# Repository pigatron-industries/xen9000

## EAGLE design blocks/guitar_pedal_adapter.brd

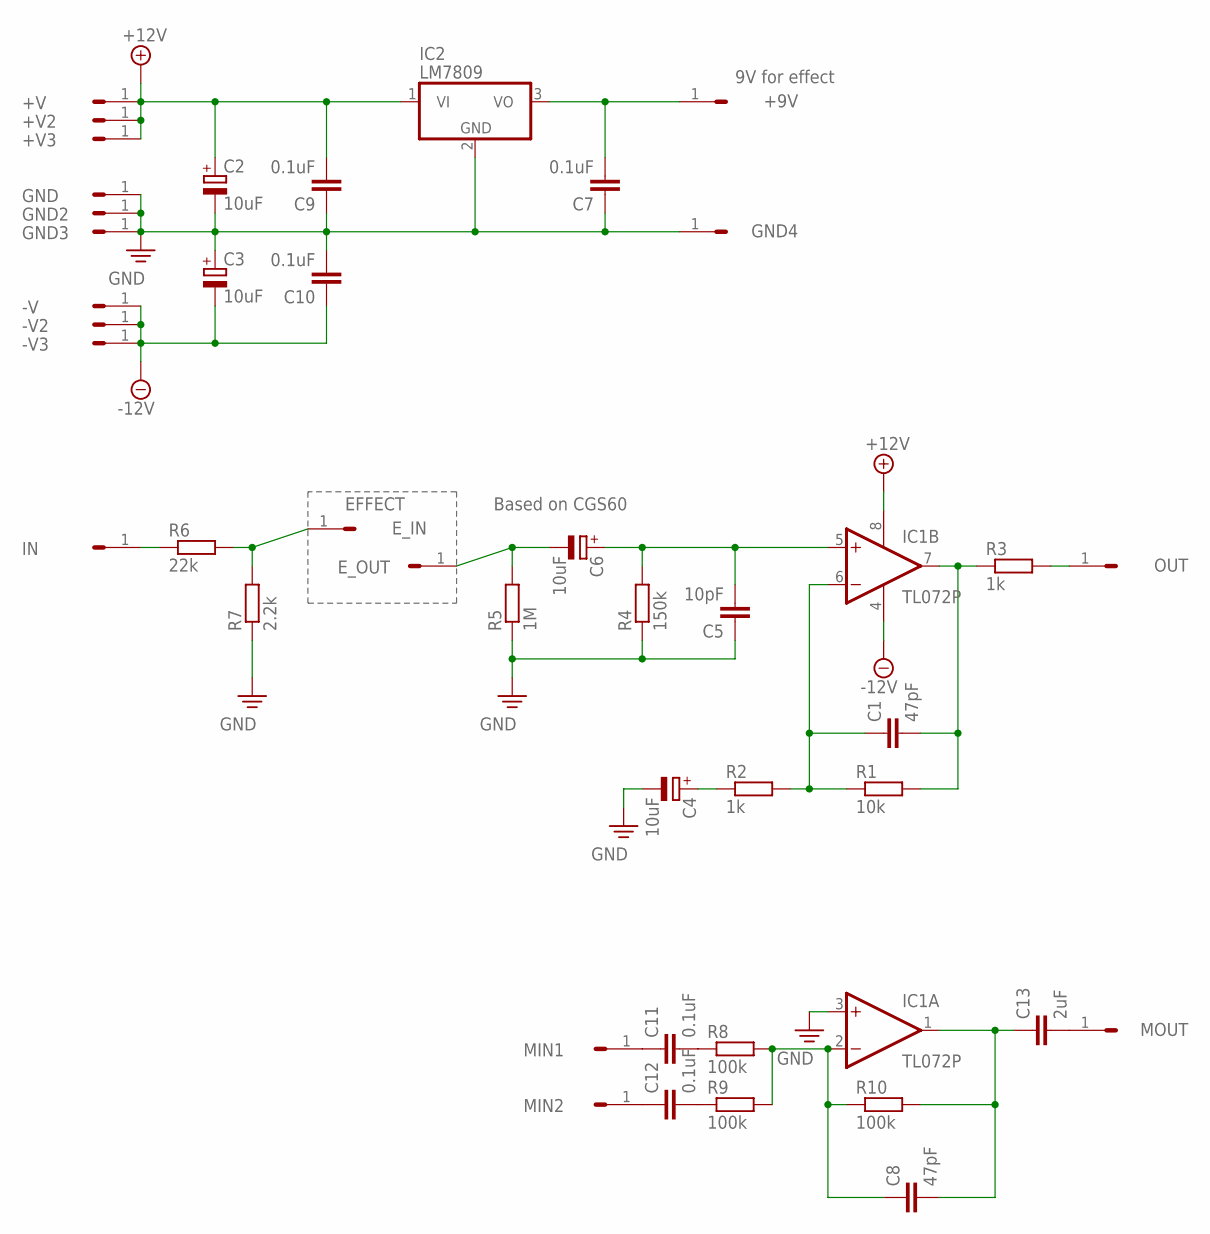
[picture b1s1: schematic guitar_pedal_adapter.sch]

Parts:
+9V: HEADER/MALE/01
+V, +V2, +V3: HEADER/MALE/01
-V, -V2, -V3: HEADER/MALE/01
C1, C8: 47pF; CERAMICDISC/5
C2, C3, C4, C6: 10uF; E2,5-6
C5: 10pF; CERAMICDISC/5
C7, C9, C10, C11, C12: 0.1uF; CERAMICDISC/5
C13: 2uF; CERAMICDISC/5
E_IN: HEADER/MALE/01
E_OUT: HEADER/MALE/01
GND, GND2, GND3, GND4: HEADER/MALE/01
IC1: TL072P; DIL08
IC2: LM7809; TO220V
IN: HEADER/MALE/01
MIN1, MIN2: HEADER/MALE/01
MOUT: HEADER/MALE/01
OUT: HEADER/MALE/01
R1: 10k; RESISTOR/7.5
R2, R3: 1k; RESISTOR/7.5
R4: 150k; RESISTOR/7.5
R5: 1M; RESISTOR/7.5
R6: 22k; RESISTOR/7.5
R7: 2.2k; RESISTOR/7.5
R8, R9, R10: 100k; RESISTOR/7.5

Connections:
+12V: +V.1, +V2.1, +V3.1, C2.+, C9.2, IC1.8 (V+), IC2.1 (VI)
-12V: -V.1, -V2.1, -V3.1, C3.-, C10.1, IC1.4 (V-)
GND: C2.-, C3.+, C4.-, C5.1, C7.1, C9.1, C10.2, GND.1, GND2.1, GND3.1, GND4.1, IC1.3 (+IN), IC2.2 (GND), R4.1, R5.1, R7.1
unnamed: C1.2, IC1.7 (OUT), R1.2, R3.1
unnamed: C1.1, IC1.6 (-IN), R1.1, R2.2
unnamed: C4.+, R2.1
unnamed: C5.2, C6.+, IC1.5 (+IN), R4.2
unnamed: E_IN.1, R6.2, R7.2
unnamed: IN.1, R6.1
unnamed: C6.-, E_OUT.1, R5.2
unnamed: +9V.1, C7.2, IC2.3 (VO)
unnamed: OUT.1, R3.2
unnamed: C8.1, IC1.2 (-IN), R8.2, R9.2, R10.1
unnamed: C8.2, C13.1, IC1.1 (OUT), R10.2
unnamed: C13.2, MOUT.1
unnamed: C11.2, R8.1
unnamed: C12.2, R9.1
unnamed: C11.1, MIN1.1
unnamed: C12.1, MIN2.1

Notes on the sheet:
EFFECT
Based on CGS60
9V for effect

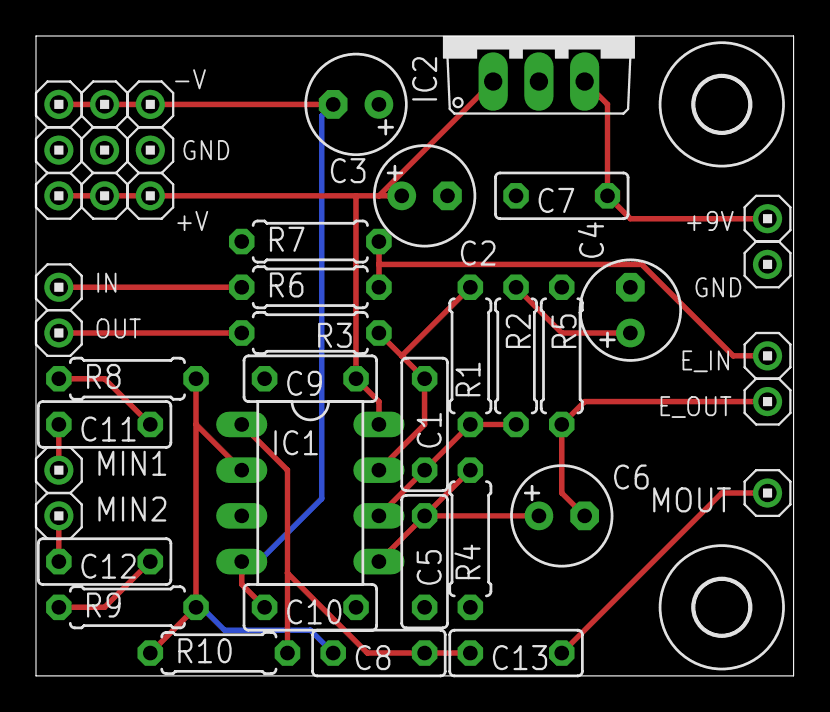
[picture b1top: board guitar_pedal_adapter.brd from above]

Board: 2 copper layers, 42.1 x 35.5 mm, 46 parts (1 on the bottom side), 19 nets.

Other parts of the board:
U$1, U$2: STANDOFF/3.0
U$3: PIGATRON-LOGO

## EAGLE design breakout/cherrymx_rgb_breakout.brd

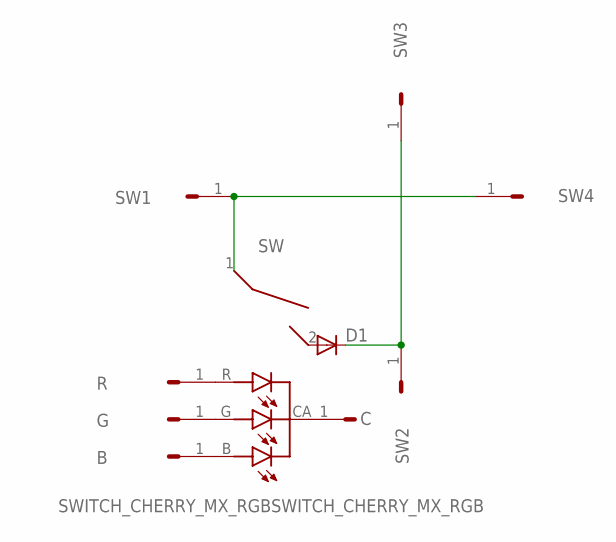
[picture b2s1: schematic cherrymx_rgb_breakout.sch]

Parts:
B: HEADER/MALE/01
C: HEADER/MALE/01
D1: 1N4148DO35-7; DO35-7
G: HEADER/MALE/01
R: HEADER/MALE/01
SW: SWITCH_CHERRY_MX_RGBSWITCH_CHERRY_MX_RGB; SWITCH_CHERRY_MX_RGB
SW1, SW2, SW3, SW4: HEADER/MALE/01

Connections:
unnamed: SW.1, SW1.1, SW4.1
unnamed: D1.A, SW.2
unnamed: B.1, SW.B (B-CAT)
unnamed: G.1, SW.G (G-CAT)
unnamed: R.1, SW.R (R-CAT)
unnamed: C.1, SW.CA (COMMON-ANODE)
unnamed: D1.C, SW2.1, SW3.1

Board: 2 copper layers, 12 parts (0 on the bottom side), 7 nets, no tracks yet.

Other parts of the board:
U$1, U$2: STANDOFF/3.0

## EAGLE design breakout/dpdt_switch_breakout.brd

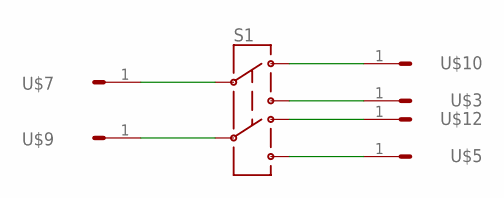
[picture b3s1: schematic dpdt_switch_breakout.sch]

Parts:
S1: SWITCH-DPDTPTH1; SWITCH-DPDT_SUBMINIATURE
U$3, U$5, U$7, U$9, U$10, U$12: HEADER/MALE/01NOBORDER; HEADER/MALE/01/NOBORDER

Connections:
unnamed: S1.6, U$5.1
unnamed: S1.1, U$10.1
unnamed: S1.3, U$3.1
unnamed: S1.2, U$7.1
unnamed: S1.4, U$12.1
unnamed: S1.5, U$9.1

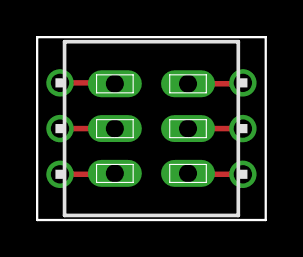
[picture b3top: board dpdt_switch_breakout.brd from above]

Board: 2 copper layers, 12.7 x 10.2 mm, 7 parts (0 on the bottom side), 6 nets.

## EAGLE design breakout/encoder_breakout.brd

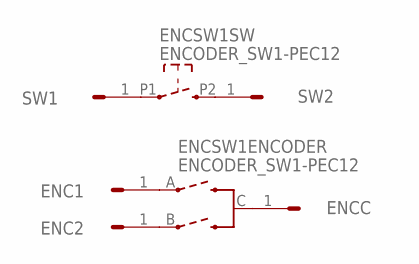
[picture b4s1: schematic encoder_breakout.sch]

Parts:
ENC1, ENC2: HEADER/MALE/01
ENCC: HEADER/MALE/01
ENCSW1: ENCODER_SW1-PEC12; PEC12_INCREMENTAL_ENCODER
SW1, SW2: HEADER/MALE/01

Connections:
unnamed: ENC1.1, ENCSW1.A
unnamed: ENC2.1, ENCSW1.B
unnamed: ENCC.1, ENCSW1.C
unnamed: ENCSW1.P1 (1), SW1.1
unnamed: ENCSW1.P2 (2), SW2.1

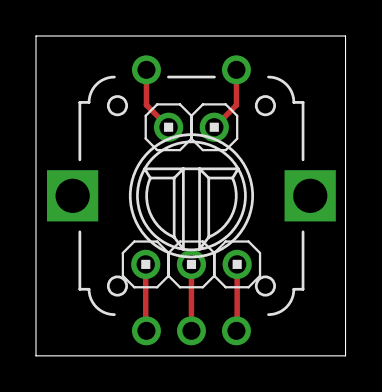
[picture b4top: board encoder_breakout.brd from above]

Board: 2 copper layers, 17.2 x 17.8 mm, 6 parts (0 on the bottom side), 5 nets.

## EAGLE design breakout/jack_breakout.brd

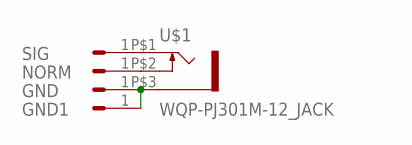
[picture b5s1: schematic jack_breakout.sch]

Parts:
GND, GND1: HEADER/MALE/01
NORM: HEADER/MALE/01
SIG: HEADER/MALE/01
U$1: WQP-PJ301M-12_JACK

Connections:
unnamed: SIG.1, U$1.P$1 (2)
unnamed: NORM.1, U$1.P$2 (3)
unnamed: GND.1, GND1.1, U$1.P$3 (1)

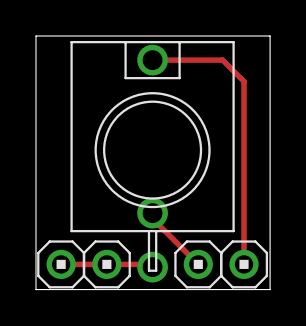
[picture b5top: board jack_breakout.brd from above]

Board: 2 copper layers, 13.0 x 14.1 mm, 5 parts (0 on the bottom side), 3 nets.

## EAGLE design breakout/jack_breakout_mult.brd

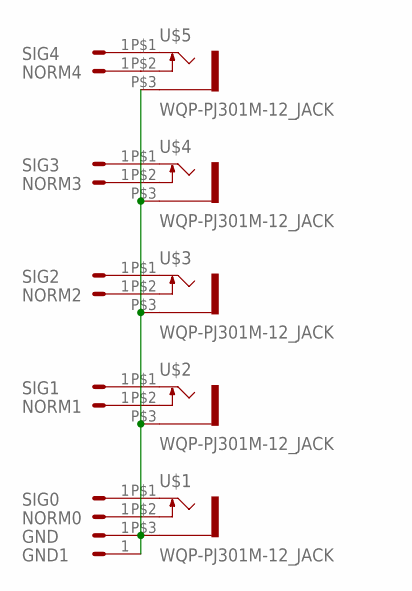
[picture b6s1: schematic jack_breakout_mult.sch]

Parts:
GND, GND1: HEADER/MALE/01
NORM0, NORM1, NORM2, NORM3, NORM4: HEADER/MALE/01
SIG0, SIG1, SIG2, SIG3, SIG4: HEADER/MALE/01
U$1, U$2, U$3, U$4, U$5: WQP-PJ301M-12_JACK

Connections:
unnamed: SIG0.1, U$1.P$1 (2)
unnamed: NORM0.1, U$1.P$2 (3)
unnamed: SIG1.1, U$2.P$1 (2)
unnamed: NORM1.1, U$2.P$2 (3)
unnamed: GND.1, GND1.1, U$1.P$3 (1), U$2.P$3 (1), U$3.P$3 (1), U$4.P$3 (1), U$5.P$3 (1)
unnamed: SIG2.1, U$3.P$1 (2)
unnamed: NORM2.1, U$3.P$2 (3)
unnamed: SIG3.1, U$4.P$1 (2)
unnamed: NORM3.1, U$4.P$2 (3)
unnamed: SIG4.1, U$5.P$1 (2)
unnamed: NORM4.1, U$5.P$2 (3)

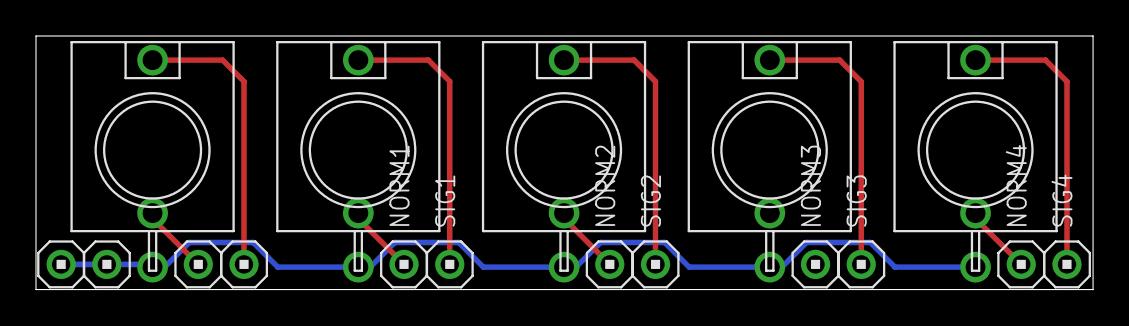
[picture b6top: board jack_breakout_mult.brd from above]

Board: 2 copper layers, 58.7 x 14.1 mm, 17 parts (0 on the bottom side), 11 nets.
